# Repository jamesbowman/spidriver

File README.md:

Full documentation is at
[spidriver.com](https://spidriver.com).

SPIDriver is a tool for controlling any SPI device from your PC's USB port.
It connects as a standard USB serial device, so there are no drivers to install.
The serial protocol is [very simple](/protocol.md),
and there are included drivers for

* Windows/Mac/Linux GUI
* Windows/Mac/Linux command-line
* Python 2 and 3
* Windows/Mac/Linux C/C++

## Contributed language bindings

The following bindings were contributed by SPIDriver community members:

* **.net** https://github.com/alandoherty/spidriver-net
* **rust** https://docs.rs/spidriver/0.1.0/spidriver/

[spidriver.com](https://spidriver.com)

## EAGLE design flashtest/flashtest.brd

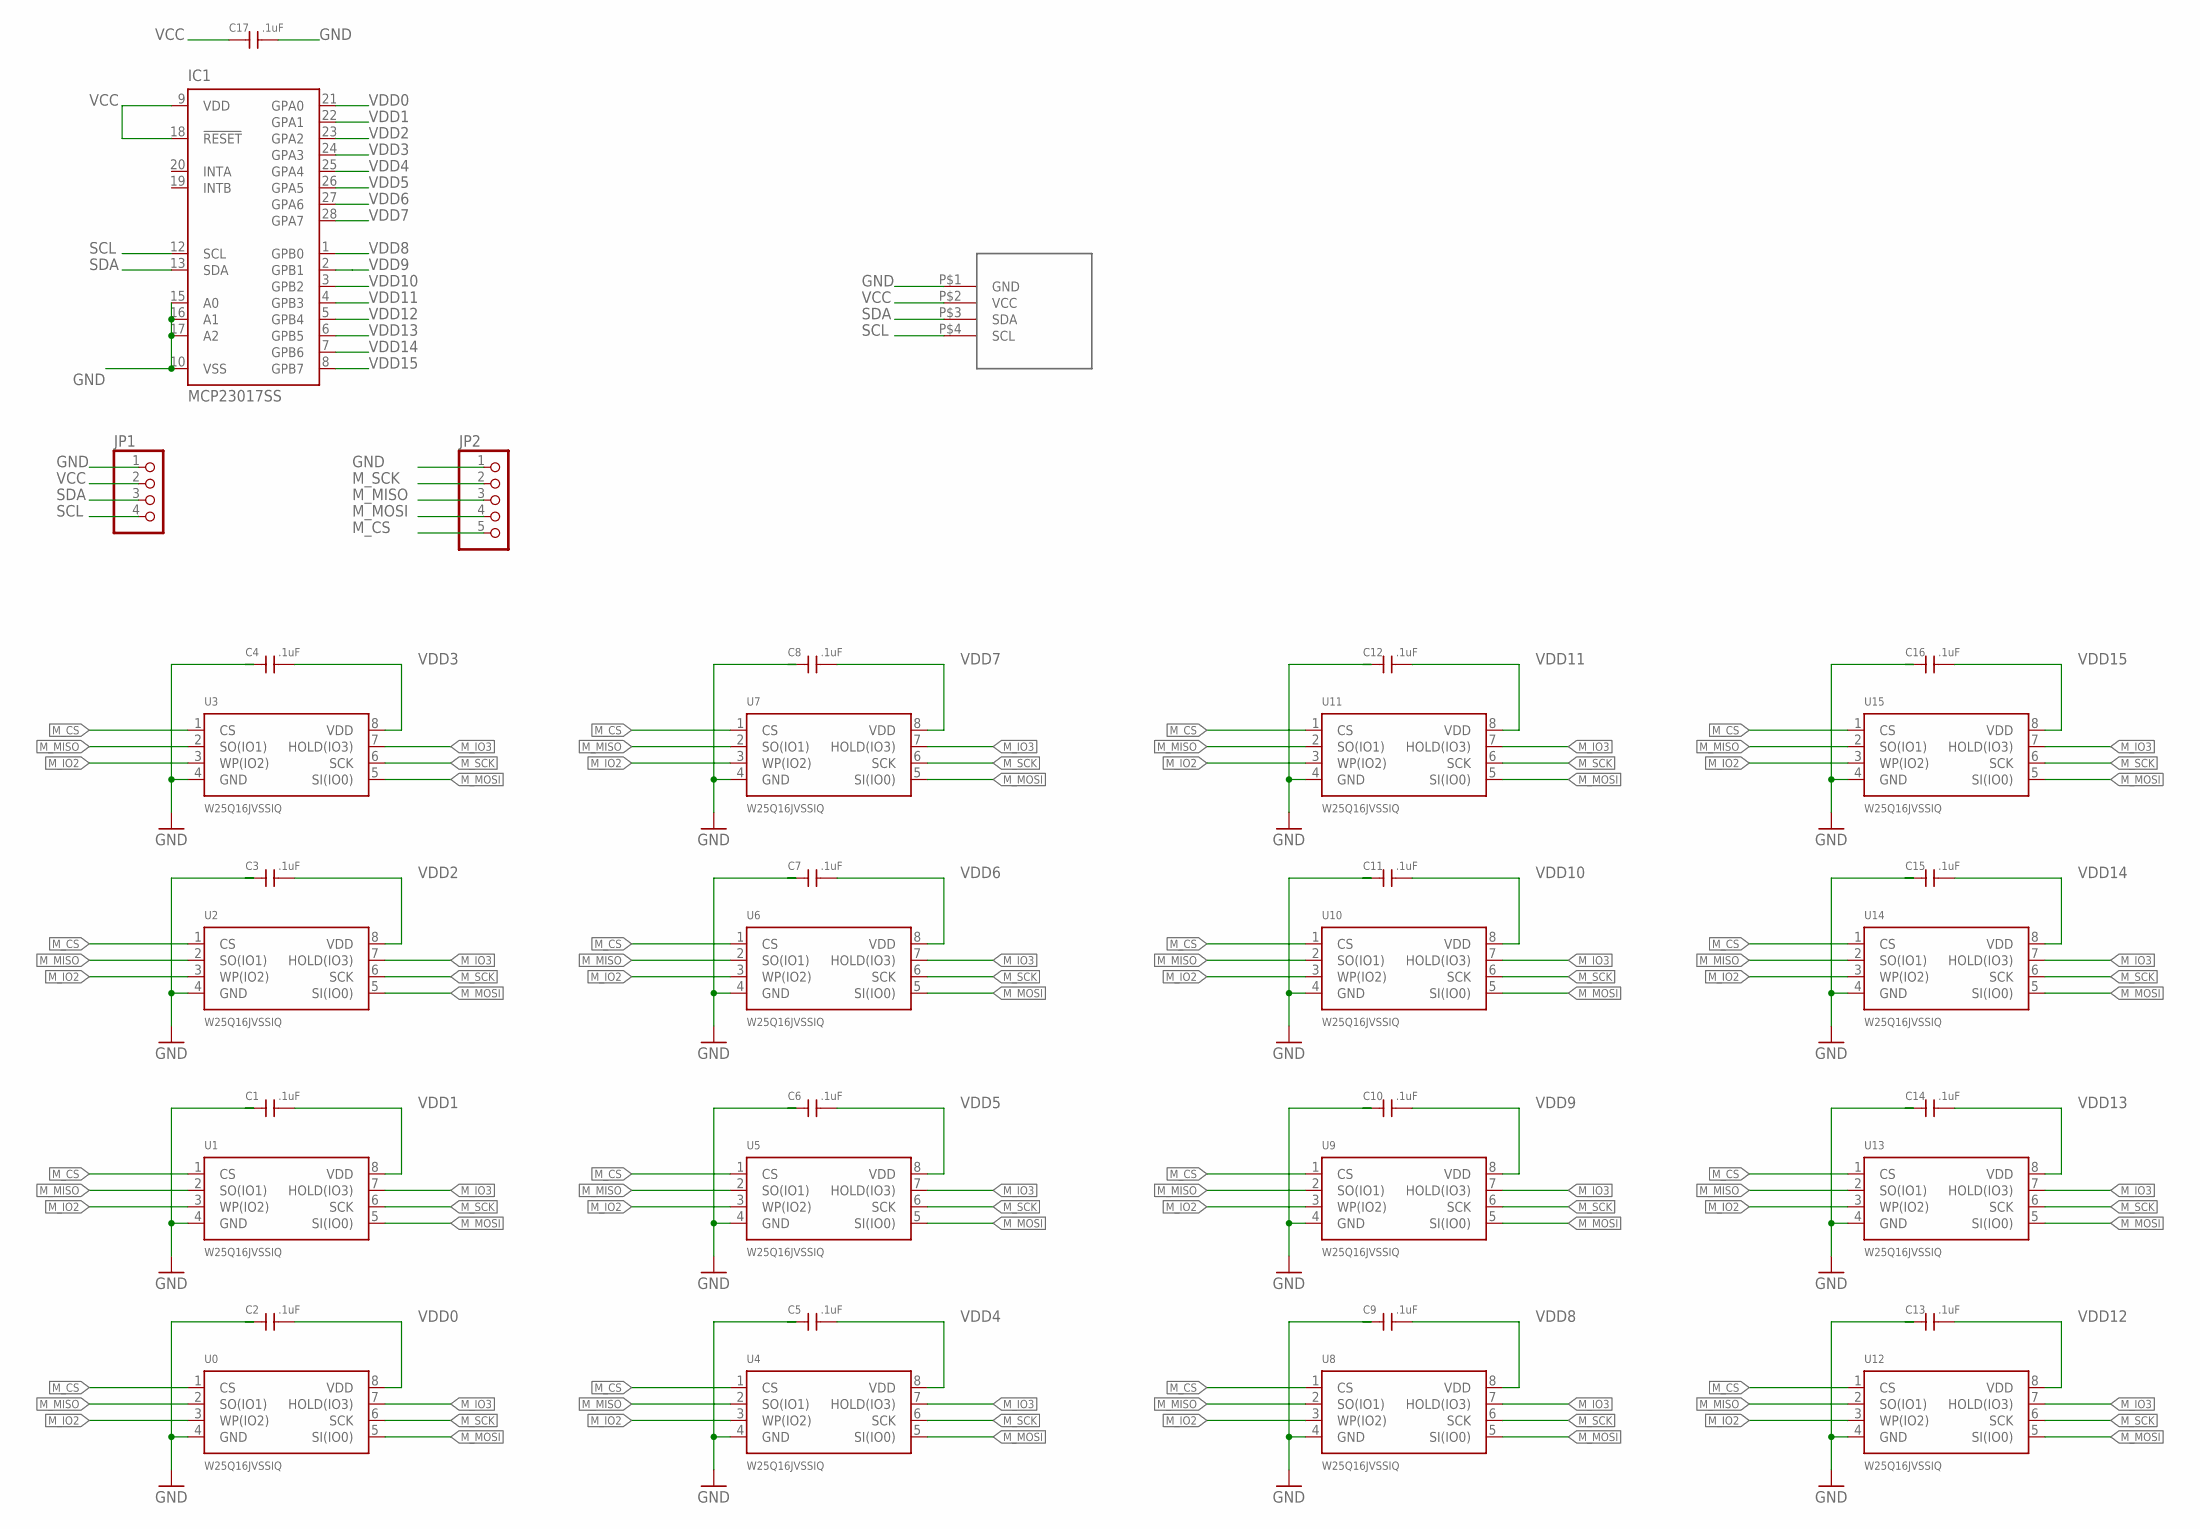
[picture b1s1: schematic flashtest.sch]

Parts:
C1, C2, C3, C4, C5, C6, C7, C8, C9, C10, C11, C12, C13, C14, C15, C16, C17: .1uF; 0603@1
IC1: MCP23017SS; SSOP28
JP1: PINHD-1X4; 1X04
JP2: PINHD-1X5; 1X05
U0, U1, U2, U3, U4, U5, U6, U7, U8, U9, U10, U11, U12, U13, U14, U15: W25Q16JVSSIQ; SOIC-8
U$1: I2C

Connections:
GND: C1.1, C2.1, C3.1, C4.1, C5.1, C6.1, C7.1, C8.1, C9.1, C10.1, C11.1, C12.1, C13.1, C14.1, C15.1, C16.1, C17.2, IC1.10 (VSS), IC1.15 (A0), IC1.16 (A1), IC1.17 (A2), JP1.1, JP2.1, U0.4 (GND), U1.4 (GND), U2.4 (GND), U3.4 (GND), U4.4 (GND), U5.4 (GND), U6.4 (GND), U7.4 (GND), U8.4 (GND), U9.4 (GND), U10.4 (GND), U11.4 (GND), U12.4 (GND), U13.4 (GND), U14.4 (GND), U15.4 (GND), U$1.P$1 (GND)
M_CS: JP2.5, U0.1 (CS), U1.1 (CS), U2.1 (CS), U3.1 (CS), U4.1 (CS), U5.1 (CS), U6.1 (CS), U7.1 (CS), U8.1 (CS), U9.1 (CS), U10.1 (CS), U11.1 (CS), U12.1 (CS), U13.1 (CS), U14.1 (CS), U15.1 (CS)
M_IO2: U0.3 (WP(IO2)), U1.3 (WP(IO2)), U2.3 (WP(IO2)), U3.3 (WP(IO2)), U4.3 (WP(IO2)), U5.3 (WP(IO2)), U6.3 (WP(IO2)), U7.3 (WP(IO2)), U8.3 (WP(IO2)), U9.3 (WP(IO2)), U10.3 (WP(IO2)), U11.3 (WP(IO2)), U12.3 (WP(IO2)), U13.3 (WP(IO2)), U14.3 (WP(IO2)), U15.3 (WP(IO2))
M_IO3: U0.7 (HOLD(IO3)), U1.7 (HOLD(IO3)), U2.7 (HOLD(IO3)), U3.7 (HOLD(IO3)), U4.7 (HOLD(IO3)), U5.7 (HOLD(IO3)), U6.7 (HOLD(IO3)), U7.7 (HOLD(IO3)), U8.7 (HOLD(IO3)), U9.7 (HOLD(IO3)), U10.7 (HOLD(IO3)), U11.7 (HOLD(IO3)), U12.7 (HOLD(IO3)), U13.7 (HOLD(IO3)), U14.7 (HOLD(IO3)), U15.7 (HOLD(IO3))
M_MISO: JP2.3, U0.2 (SO(IO1)), U1.2 (SO(IO1)), U2.2 (SO(IO1)), U3.2 (SO(IO1)), U4.2 (SO(IO1)), U5.2 (SO(IO1)), U6.2 (SO(IO1)), U7.2 (SO(IO1)), U8.2 (SO(IO1)), U9.2 (SO(IO1)), U10.2 (SO(IO1)), U11.2 (SO(IO1)), U12.2 (SO(IO1)), U13.2 (SO(IO1)), U14.2 (SO(IO1)), U15.2 (SO(IO1))
M_MOSI: JP2.4, U0.5 (SI(IO0)), U1.5 (SI(IO0)), U2.5 (SI(IO0)), U3.5 (SI(IO0)), U4.5 (SI(IO0)), U5.5 (SI(IO0)), U6.5 (SI(IO0)), U7.5 (SI(IO0)), U8.5 (SI(IO0)), U9.5 (SI(IO0)), U10.5 (SI(IO0)), U11.5 (SI(IO0)), U12.5 (SI(IO0)), U13.5 (SI(IO0)), U14.5 (SI(IO0)), U15.5 (SI(IO0))
M_SCK: JP2.2, U0.6 (SCK), U1.6 (SCK), U2.6 (SCK), U3.6 (SCK), U4.6 (SCK), U5.6 (SCK), U6.6 (SCK), U7.6 (SCK), U8.6 (SCK), U9.6 (SCK), U10.6 (SCK), U11.6 (SCK), U12.6 (SCK), U13.6 (SCK), U14.6 (SCK), U15.6 (SCK)
SCL: IC1.12 (SCL), JP1.4, U$1.P$4 (SCL)
SDA: IC1.13 (SDA), JP1.3, U$1.P$3 (SDA)
VCC: C17.1, IC1.9 (VDD), IC1.18 (!RESET), JP1.2, U$1.P$2 (VCC)
VDD0: C2.2, IC1.21 (GPA0), U0.8 (VDD)
VDD1: C1.2, IC1.22 (GPA1), U1.8 (VDD)
VDD2: C3.2, IC1.23 (GPA2), U2.8 (VDD)
VDD3: C4.2, IC1.24 (GPA3), U3.8 (VDD)
VDD4: C5.2, IC1.25 (GPA4), U4.8 (VDD)
VDD5: C6.2, IC1.26 (GPA5), U5.8 (VDD)
VDD6: C7.2, IC1.27 (GPA6), U6.8 (VDD)
VDD7: C8.2, IC1.28 (GPA7), U7.8 (VDD)
VDD8: C9.2, IC1.1 (GPB0), U8.8 (VDD)
VDD9: C10.2, IC1.2 (GPB1), U9.8 (VDD)
VDD10: C11.2, IC1.3 (GPB2), U10.8 (VDD)
VDD11: C12.2, IC1.4 (GPB3), U11.8 (VDD)
VDD12: C13.2, IC1.5 (GPB4), U12.8 (VDD)
VDD13: C14.2, IC1.6 (GPB5), U13.8 (VDD)
VDD14: C15.2, IC1.7 (GPB6), U14.8 (VDD)
VDD15: C16.2, IC1.8 (GPB7), U15.8 (VDD)

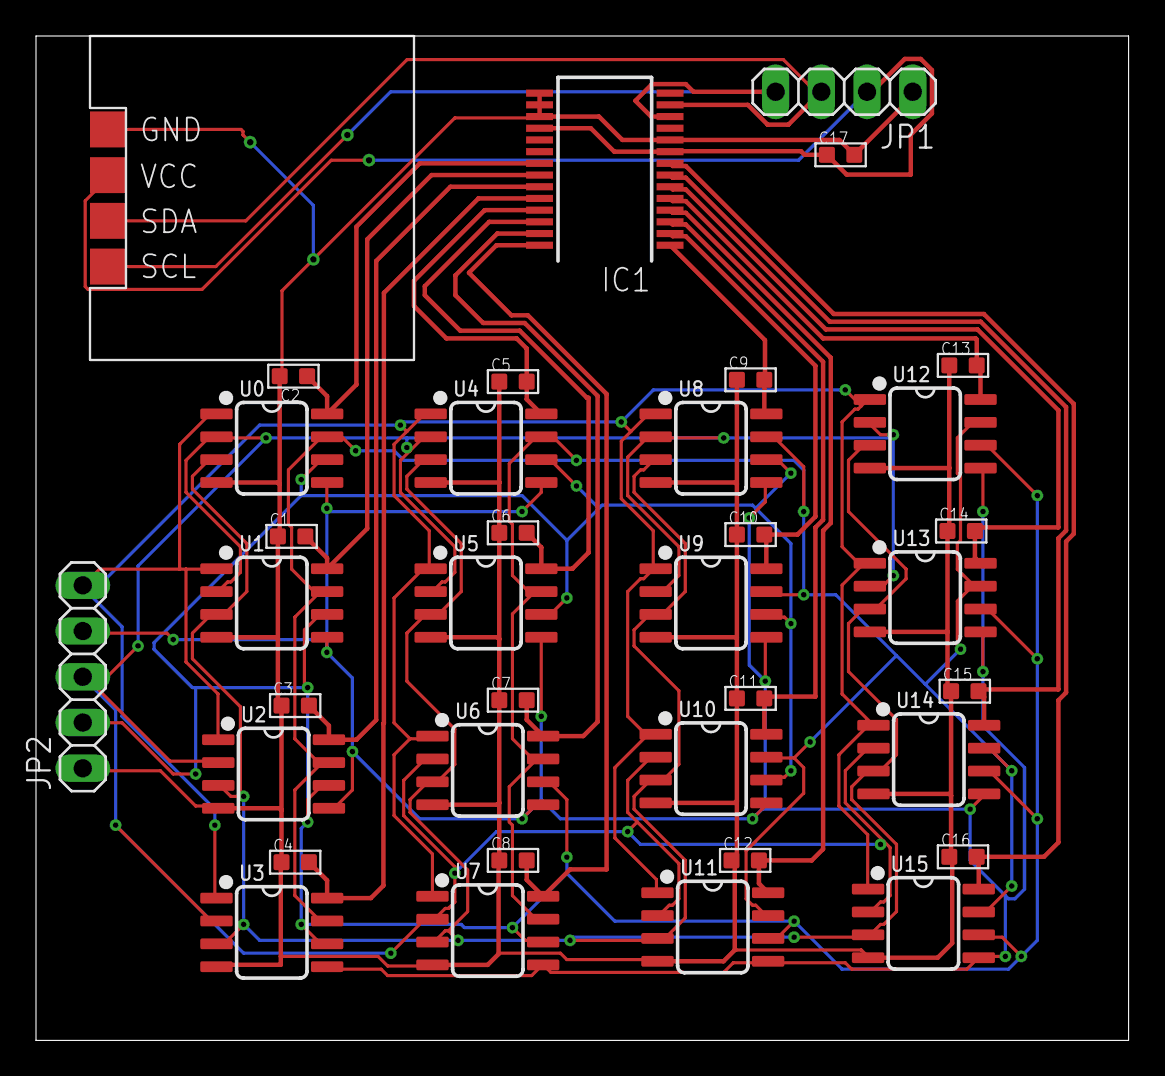
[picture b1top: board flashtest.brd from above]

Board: 2 copper layers, 60.7 x 55.8 mm, 37 parts (0 on the bottom side), 26 nets.

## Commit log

2018-04-03 First images
2018-04-03 Describe features
2018-04-03 Close-up image
2018-04-03 Link to PCB image
2018-04-03 Feature list
2018-04-03 Add logo
2018-04-03 Fix typos
2018-05-03 C/C++ bindings for Linux
2018-05-03 Example of command-line usage
2018-05-03 Missing stdlib.h
2018-05-03 Using cfmakeraw() avoids hang on first read on rPi
2018-05-04 Python library import
2018-05-04 Version string in one place
2018-05-04 Enable Travis
2018-05-04 Travis fix
2018-05-04 Remve support for Python 2.6
2018-05-04 Add C utilities to Travis test
2018-05-05 LED string driver
2018-05-05 Slow down LED cycling
2018-05-05 Add writeread method
2018-05-05 Atmega ISP example
2018-05-06 Add CCITT CRC to C implementation
2018-05-07 Start of Gtk GUI
2018-05-07 Text entry
2018-05-08 loadimage demo
2018-05-09 CRC updates on both write and writeread
2018-05-09 Rename CRC field to ccitt_crc
2018-05-09 Report on clock drift
2018-05-12 Thrash sample
2018-05-14 Add support for "detach" command
2018-05-14 Full Atmega programmer
2018-05-22 Minor cleanups for Python2/3
2018-05-22 Format for 480x272
2018-05-22 Accept device name as first arg
2018-05-22 Accept device on command line
2018-06-04 Protocol writeup
2018-06-04 Document x command
2018-06-15 Add example of building and running command-line tool
2018-06-22 Import the win32 GUI
2018-06-22 Static link libstdc++, switch to true spidriver
2018-06-22 Win32 command-line takes device name
2018-06-22 Remove accidentally added file
2018-06-22 Silence more type warnings
2018-06-22 Rename Mac/Linux executable to spicl
2018-06-22 Fix missing/bad device flow
2018-06-22 Add firmware and hardware directories
2018-06-22 Clean up comments
2018-06-22 Fix phrasing
2018-06-22 import PCBnew
2018-06-25 Win32 GUI version looking OK
2018-07-06 Initial import, LCD panel sample
2018-07-06 Checkpoint, refactoring
2018-07-06 Refactored
2018-07-10 Properly resize and crop images for display
2018-07-10 Grace Hopper test image
2018-07-11 Sort imports. Remove unused
2018-07-11 Add encoding declarations
2018-07-11 PEP8 docstrings & remove redundant parens
2018-07-11 PEP8 whitespace
2018-07-11 Fix some print statements
2018-07-31 Add 256x256 icon. Use as Windows icon
2018-07-31 Remove Python 3.2 - no longer supported?
2018-07-31 Proper Windows installer using NSIS
2018-08-01 Place holder for wx GUI
2018-08-01 Clean up GTK gui
2018-08-02 Signals hooked up
2018-08-02 All widgets functional
2018-08-03 Device selection
2018-08-03 Clean up for Python3 and MacOS
2018-08-03 Proper name
2018-08-03 Cope with missing directory properly
2018-08-03 UI cleanups
    Enter key does transfer
    Device picker combobox is read-only
    Use monospace for logginmg window
2018-08-25 Update for actual module used
2018-08-25 Assert RESET properly
2018-08-26 Fix for Python 2
2018-08-26 Print bytes as unsigned
2018-08-26 Flash sample initial version
2018-08-26 Clean up for Python 3
2018-08-27 Rebuild everything script
2018-08-30 Implement behavior described in #7
2018-08-30 In the win32 common code, if portname starts with 'C' insert the prefix \\.\
    [#6]
2018-09-01 First cut of the iceprog
2018-09-01 Removed extraneous material
2018-09-02 Update with notes for Windows users
2018-09-02 minor edit
2018-09-02 Clean up
2018-09-02 Point everyone to official page
2018-09-04 Enable testing on both Linux and OSX
2018-09-04 Attempt reduced matrix
2018-09-04 testall exit on failed command
2018-09-04 fix baud rate on osx?
2018-09-04 move pyserial around
2018-09-04 Travis: try doing install --user
2018-09-04 Travis osx: testall is a shell script
2018-09-04 Travis osx: don't do --user install
2018-09-04 osx: include ioctl.h
2018-09-05 osx: properly set 460800 baud
2018-09-05 Pure Python RGB565 encoder for better portability
2018-09-07 Proper flash example, confirmed with ESP8266
2019-01-13 python/samples/flash.py: Add size option
    Some flash chips do not provide the flash size in the second byte of the
    device ID, which can either cause the wrong number of bytes to be
    read/written or cause idcode() to be called infinitely. The user must
    check their chip's datasheet to know whether its device ID includes its
    size or they need to specify the size with the -s option.
    Read tested with an Atmel AT26DF321 (manufacturer ID 0x1F, device ID
2019-01-13 .gitignore: Exclude built objects and executables
2019-04-28 Update home URL
2019-04-28 Clean compile on win32
2019-05-11 Modifications for MSVC
2019-07-01 Recognize size fields of 1-7 as valid. For FeRAM
    [#19]
2019-07-23 Multi flash/FRAM test board
2019-07-26 Work with new API
2020-01-24 Add links to .net and rust drivers
2021-02-10 Docs first attempt
2021-02-11 Generate all formats
2021-02-11 Version bump to 1.0.0
2021-02-12 Readthedocs badge
2021-03-31 Updates for spidriver2
2021-03-31 Version 1.1.0
2021-03-31 Mode support for spidriver2
2021-09-04 Document setmode
2021-09-04 version bump for documentation of setmode
2022-01-07 gui.py: Fixup to avoid deprecated warnings
2022-01-07 gui.py: Fix Button code to work correctly
    * Dont use deprecated function.
2022-02-25 spicl: improve command arg checking
    For 'w' and 'r', a missing argument would cause a segfault. For 'a',
    'b' and 'm', the command would just be ignored. Lets try to improve that
    a little.
2022-02-25 spicl: repeat sequence
    Really nice for clearing a display that needs an enable/disable around
    each byte.
2022-03-05 Fix warnings when building with warnings enabled
2022-05-06 Update st7735s.py
    Replace the `array.array('B', d565h.tostring())` with `array.array('B', d565h.tobytes())` to match deprecation in Python3.
2022-08-16 port to python3
2023-02-07 Fix link
